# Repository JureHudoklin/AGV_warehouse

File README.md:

# AGV_warehouse

This is a project I am currently working on. I am working on this also as a final project for my undergraduate degree (diploma). In this project I am developing and programing a robot ("robot platform") that could be used in simulation of a warehouse environment. In a simulation these robots would have to found their way around warehouse based on the input provided by the master computer. Each robot has to follow guiding lines, know his position based on ground markings, be able to autonomously charge itself, stop and report in case of obstacles and load cargo from designated stations. 

I already completed the robot design phase. I have designed the pcb plate as well as the whole assembly. The robot will be assembled in next few weeks when I receive all the necessary parts. This part of the project is located in ./agv-skladiscni-v1/ (KiCad files) and ./Step_modeli/ (step models of robot and pcb plate).

The logic of the robot will run on a BeagleBone blue board. The board will run a ROS operating system. This is the part I have just started working on. I am writing the code in C++ which is the first bigger program I am writing in C++. I expect to learn C++ quite well when I am finished with this project. The code part of this project can be found in the ./catkin_ws/src/ folder. I have not written a lot of code yet bet the currently working part is locate in robot_control package 

**./catkin_ws/src/robot_control/src/...**

<image src="robot_v4/step_modeli/robot_picture.jpg">

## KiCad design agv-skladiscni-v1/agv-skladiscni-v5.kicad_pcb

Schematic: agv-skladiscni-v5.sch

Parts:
IC1, IC2: NLAST4051DTR2G; SOP65P640X120-16N; Manufacturer_Part_Number NLAST4051DTR2G
J1: TOF_0; SolderWirePad_1x05_P3.175mm_Drill0.8mm
J2: TOF_1; SolderWirePad_1x05_P3.175mm_Drill0.8mm
J3: GP1; SolderWirePad_2x03_P3.175mm_Drill0.8mm
J4: I2C; SolderWirePad_1x04_P3.175mm_Drill0.8mm
J5: ADC; SolderWirePad_2x03_P3.175mm_Drill0.8mm
J6: GP0; SolderWirePad_2x03_P3.175mm_Drill0.8mm
Q1, Q2: BSS138; SOT-23
R1, R2, R7, R8, R13, R14, R23, R24: 35R; R_0805_2012Metric_Pad1.15x1.40mm_HandSolder
R3, R4, R5, R6, R9, R10, R11, R12, R15, R16, R17, R18, R19, R20, R21, R22, R25, R26, R27, R28, R29, R30: 10K; R_0805_2012Metric_Pad1.15x1.40mm_HandSolder
U1, U2, U3, U4, U5, U6, U7, U8, U9, U10, U11, U12, U13, U14, U15, U16: QRE1113GR; Everlight_ITR8307F43

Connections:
+1V8: J5.2, R3.1, R4.1, R5.1, R6.1, R9.1, R10.1, R11.1, R12.1, R15.1, R16.1, R20.1, R21.1, R25.1, R26.1, R27.1, R28.1
+3V3: IC1.16, IC2.16, J1.4, J2.4, J3.2, J4.2, J6.2, U1.2 (A), U3.2 (A), U5.2 (A), U7.2 (A), U9.2 (A), U11.2 (A), U13.2 (A), U15.2 (A)
A0: IC1.3, J5.3
A1: IC2.3, J5.4
DIG0: IC1.9, IC2.9, J6.3, R22.1
DIG1: IC1.10, IC2.10, J6.4, R19.1
DIG2: IC1.11, IC2.11, J6.5, R18.1
GND: IC1.7, IC1.8, IC2.7, IC2.8, J1.5, J2.5, J3.1, J4.1, J5.1, J6.1, Q1.2, Q2.2, R17.2, R18.2, R19.2, R22.2, R29.2, R30.2, U1.4 (E), U2.4 (E), U3.4 (E), U4.4 (E), U5.4 (E), U6.4 (E), U7.4 (E), U8.4 (E), U9.4 (E), U10.4 (E), U11.4 (E), U12.4 (E), U13.4 (E), U14.4 (E), U15.4 (E), U16.4 (E)
LED0,1: Q1.3, R2.2, R8.2, R14.2, R24.2
LED10,11: Q2.3, R1.2, R7.2, R13.2, R23.2
LEDS: J6.6, Q1.1, Q2.1, R17.1
unnamed: IC1.6, R29.1
unnamed: IC2.6, R30.1
unnamed: R1.1, U2.1 (K)
unnamed: R2.1, U4.1 (K)
unnamed: R7.1, U6.1 (K)
unnamed: R8.1, U8.1 (K)
unnamed: R13.1, U10.1 (K)
unnamed: R14.1, U12.1 (K)
unnamed: R23.1, U14.1 (K)
unnamed: R24.1, U16.1 (K)
unnamed: U1.1 (K), U2.2 (A)
unnamed: U3.1 (K), U4.2 (A)
unnamed: U5.1 (K), U6.2 (A)
unnamed: U7.1 (K), U8.2 (A)
unnamed: U9.1 (K), U10.2 (A)
unnamed: U11.1 (K), U12.2 (A)
unnamed: U13.1 (K), U14.2 (A)
unnamed: U15.1 (K), U16.2 (A)
SCL: J1.3, J2.3, J4.3
SDA: J1.2, J2.2, J4.4
SEN0: IC1.13, R4.2, U3.3 (C)
SEN1: IC1.1, R6.2, U4.3 (C)
SEN2: IC1.15, R10.2, U7.3 (C)
SEN3: IC1.2, R12.2, U8.3 (C)
SEN4: IC1.14, R16.2, U11.3 (C)
SEN5: IC1.5, R21.2, U12.3 (C)
SEN6: IC1.12, R26.2, U15.3 (C)
SEN7: IC1.4, R28.2, U16.3 (C)
SEN8: IC2.13, R3.2, U1.3 (C)
SEN9: IC2.1, R5.2, U2.3 (C)
SEN10: IC2.15, R9.2, U5.3 (C)
SEN11: IC2.2, R11.2, U6.3 (C)
SEN12: IC2.14, R15.2, U9.3 (C)
SEN13: IC2.5, R20.2, U10.3 (C)
SEN14: IC2.12, R25.2, U13.3 (C)
SEN15: IC2.4, R27.2, U14.3 (C)
Xshut_0: J1.1, J3.3
Xshut_1: J2.1, J3.4

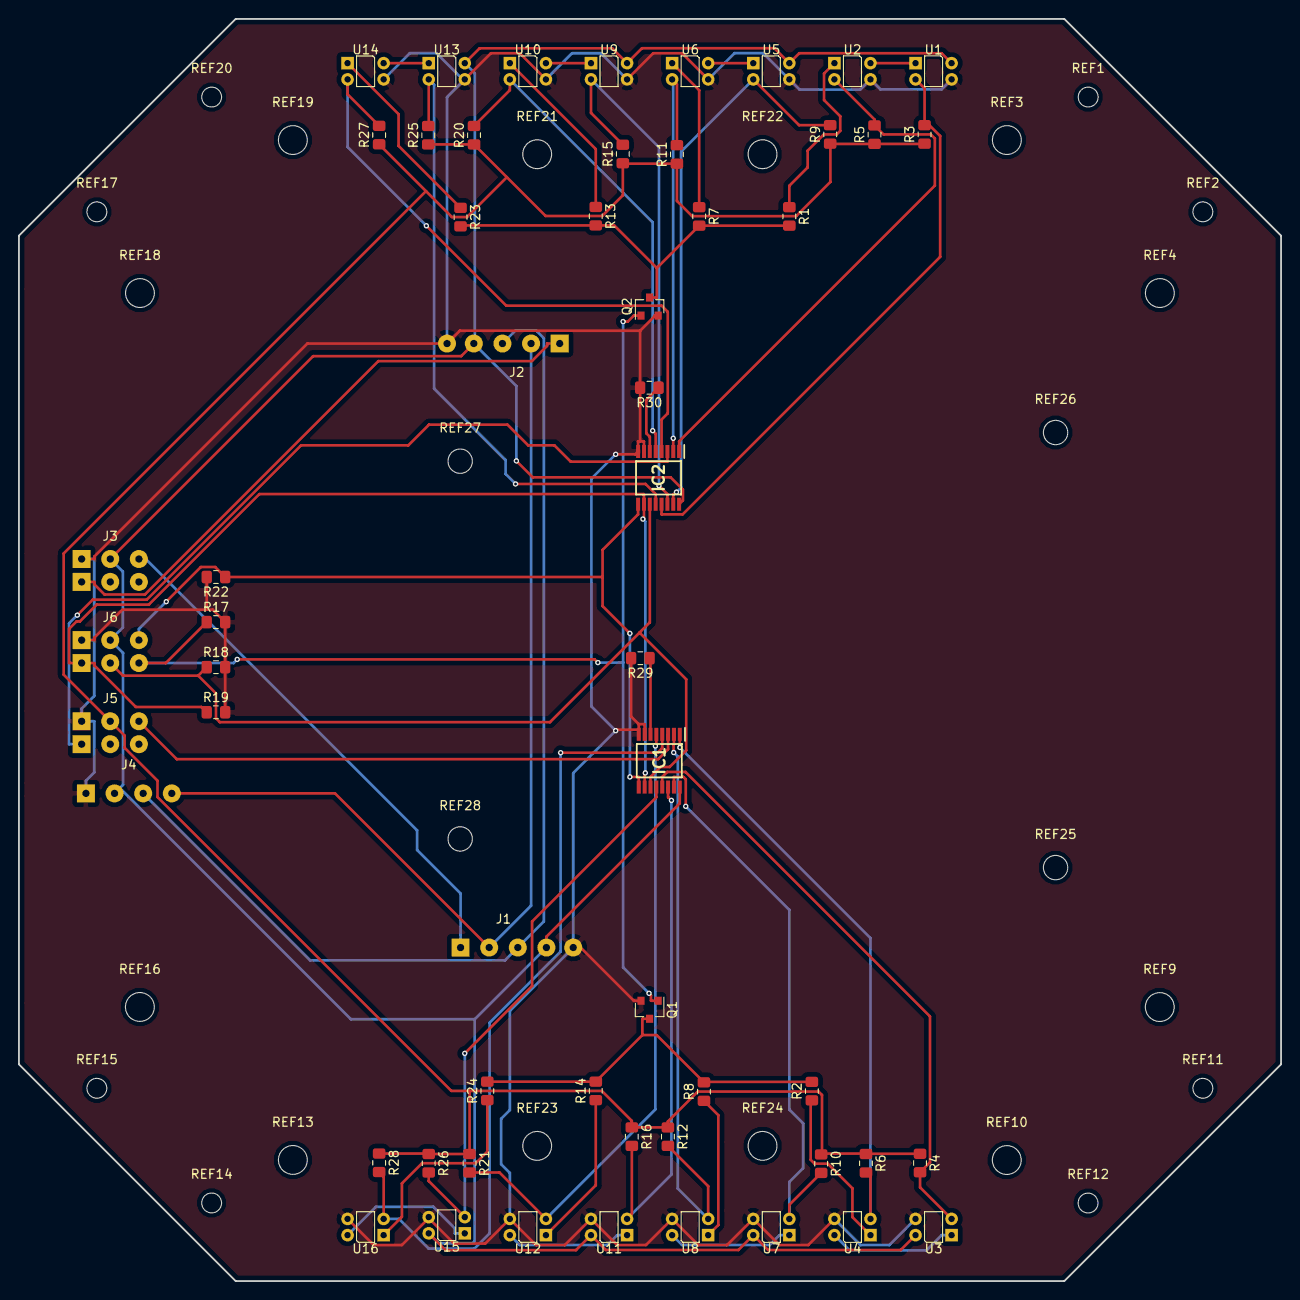
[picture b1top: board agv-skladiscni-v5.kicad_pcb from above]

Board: 2 copper layers, 140.0 x 140.0 mm, 80 parts (0 on the bottom side), 49 nets.

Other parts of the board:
REF1, REF2, REF11, REF12, REF14, REF15, REF17, REF20 : MountingHole_2.2mm_M2
REF3, REF4, REF9, REF10, REF13, REF16, REF18, REF19, REF21, REF22, REF23, REF24: MountingHole_3.2mm_M3
REF25, REF26, REF27, REF28: MountingHole_2.7mm_M2.5

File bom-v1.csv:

Refs,Value,Footprint,Quantity,MFR,MPN,SPR,SPN
J4,I2C,Connector_Wire:SolderWirePad_1x04_P3.175mm_Drill0.8mm,1,-,-,-,-
J1,TOF_0,Connector_Wire:SolderWirePad_1x05_P3.175mm_Drill0.8mm,1,-,-,-,-
J2,TOF_1,Connector_Wire:SolderWirePad_1x05_P3.175mm_Drill0.8mm,1,-,-,-,-
J5,ADC,Connector_Wire:SolderWirePad_2x03_P3.175mm_Drill0.8mm,1,-,-,-,-
J6,GP0,Connector_Wire:SolderWirePad_2x03_P3.175mm_Drill0.8mm,1,-,-,-,-
J3,GP1,Connector_Wire:SolderWirePad_2x03_P3.175mm_Drill0.8mm,1,-,-,-,-
IC1;IC2,NLAST4051DTR2G,NLAST4051DTR2G:SOP65P640X120-16N,2,,-NLAST4051DTR2G,-,-
U3;U4;U7;U8;U11;U12;U15;U16;U1;U2;U5;U6;U9;U10;U13;U14,QRE1113GR,OptoDevice:Everlight_ITR8307F43,16,-,-QRE1113GR,-,-
Q1;Q2,BSS138,Package_TO_SOT_SMD:SOT-23,2,-,-BSS138,-,-
R4;R6;R10;R12;R16;R21;R26;R28;R3;R5;R9;R11;R15;R20;R25;R27;R29;R30;R17;R18;R19;R22,10K,Resistor_SMD:R_0805_2012Metric_Pad1.15x1.40mm_HandSolder,22,-,-CRCW080510K0FKEAC,-,-
R2;R8;R14;R24;R1;R7;R13;R23,35R,Resistor_SMD:R_0805_2012Metric_Pad1.15x1.40mm_HandSolder,8,-,-ERJ-6ENF35R7V,-,-

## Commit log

2019-01-29 code
2019-01-29 steps
2019-02-10 Changes to robot pkg
2019-02-10 test
2019-02-10 modified: catkin_ws/src/robot_control/src/robot_control_cpp.cpp
2019-02-11 modified: catkin_ws/src/robot/CMakeLists.txt modified: catkin_ws/src/robot/launch/robot_launch.launch modified: catkin_ws/src/robot/src/robot_cpp.cpp modified: catkin_ws/src/robot_control/CMakeLists.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
2019-02-12 modified: catkin_ws/src/robot/msg/Control.msg modified: catkin_ws/src/robot/src/robot_cpp.cpp new file: catkin_ws/src/robot/src/robot_logic.cpp modified: catkin_ws/src/robot_control/src/robot_control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
2019-02-13 modified: catkin_ws/src/robot/launch/robot_launch.launch modified: catkin_ws/src/robot/src/robot_cpp.cpp
2019-02-16 Robot calculate velocities
2019-02-19 PID controls for velocities
2019-02-19 PID controler
2019-02-27 Removed error in gpio setup
2019-03-12 PID change
2019-03-12 Control changes
2019-03-12 PID working
2019-03-13 Global koordinate system / begining
2019-03-31 small crections
2019-04-06 Position corection
2019-04-07 action MoveRobot
2019-04-07 ignore and remove .vscode files
2019-04-07 add missing files
2019-04-09 Changes to CMakeFIle, Finished MoveRobot action server, started on ActionClient in main robot node
2019-04-09 Changes to CMakeFIle, Finished MoveRobot action server, started on Ac…
2019-04-09 Small error corections
2019-04-10 Acition MoveRobot
2019-04-28 Changes to MoveRobot bug fixes
2019-04-28 sensors
2019-04-28 random changes
2019-05-01 new MoveRobot logic -> untested
2019-05-01 MoveRobot working
2019-05-11 changed to Velocity PID with FeedForward
2019-05-12 Fixed errors in new PID control. Calibrated PID control settings. Need to add anti integrator winduip in PID
2019-06-17 Sensors error fixes
2019-06-18 FollowLine acition dela, popravljen PID spet dela, potrebno se nastaviti koeficiente, odstrani vse dodane ROS_INFO za testiranje
2019-06-19 Some code cleanup
2019-06-19 code clenup
2019-06-19 Corrected an error in robot move and robot position calculation. Set new koeficients for file follow
2019-06-20 added TOF
2019-07-07 Some cleanup
2019-07-07 added robot header
